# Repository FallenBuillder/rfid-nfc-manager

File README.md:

# rfid-nfc-manager
This repository consists of schematics, PCB layouts, code and 3D models for a rfid,nfc manager.

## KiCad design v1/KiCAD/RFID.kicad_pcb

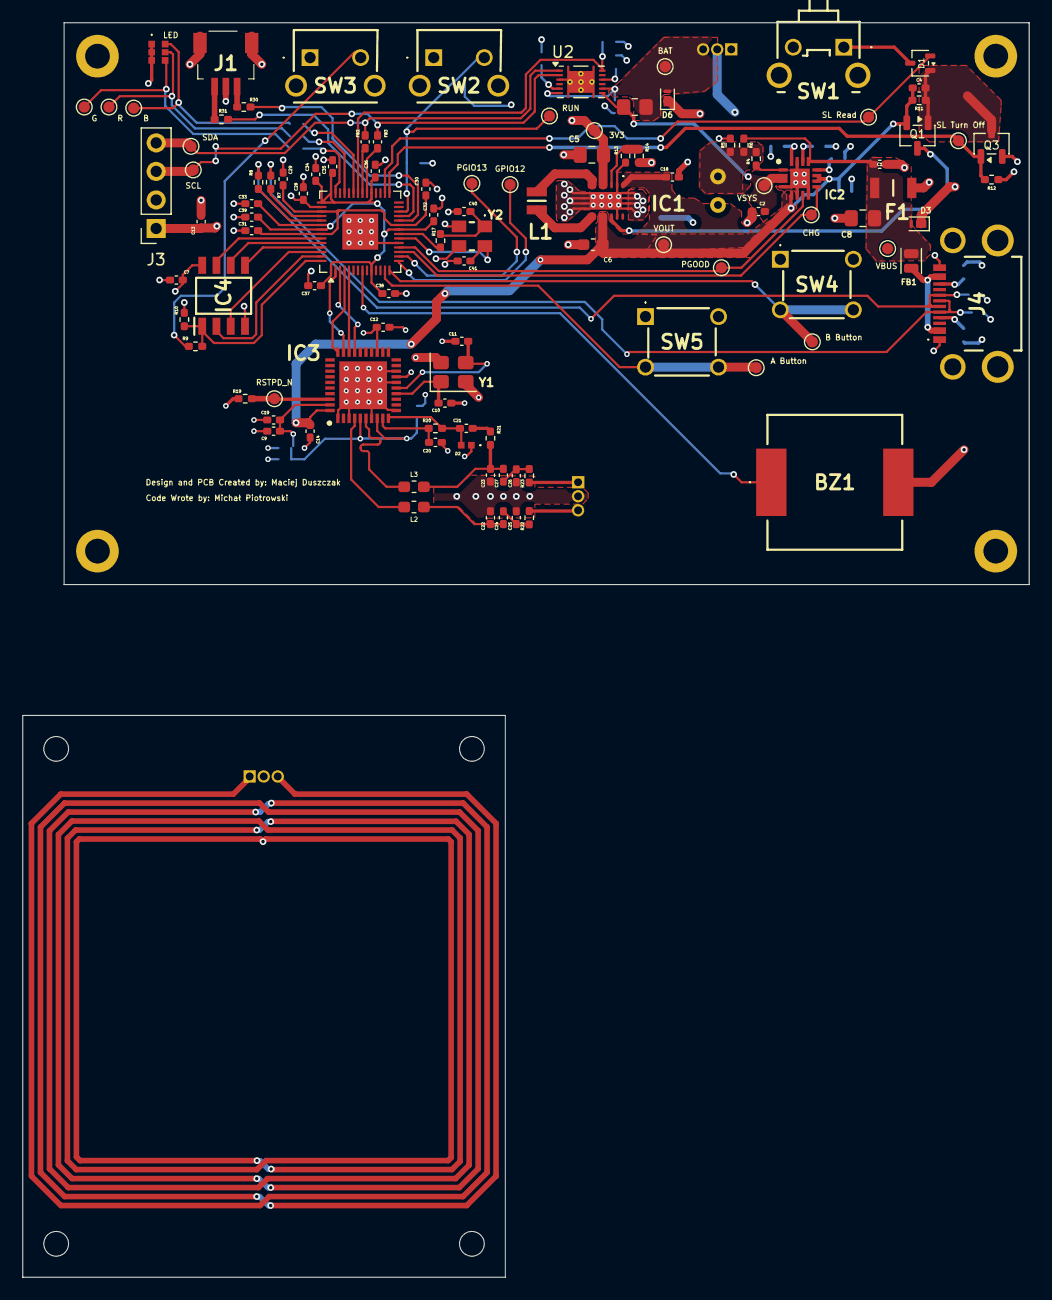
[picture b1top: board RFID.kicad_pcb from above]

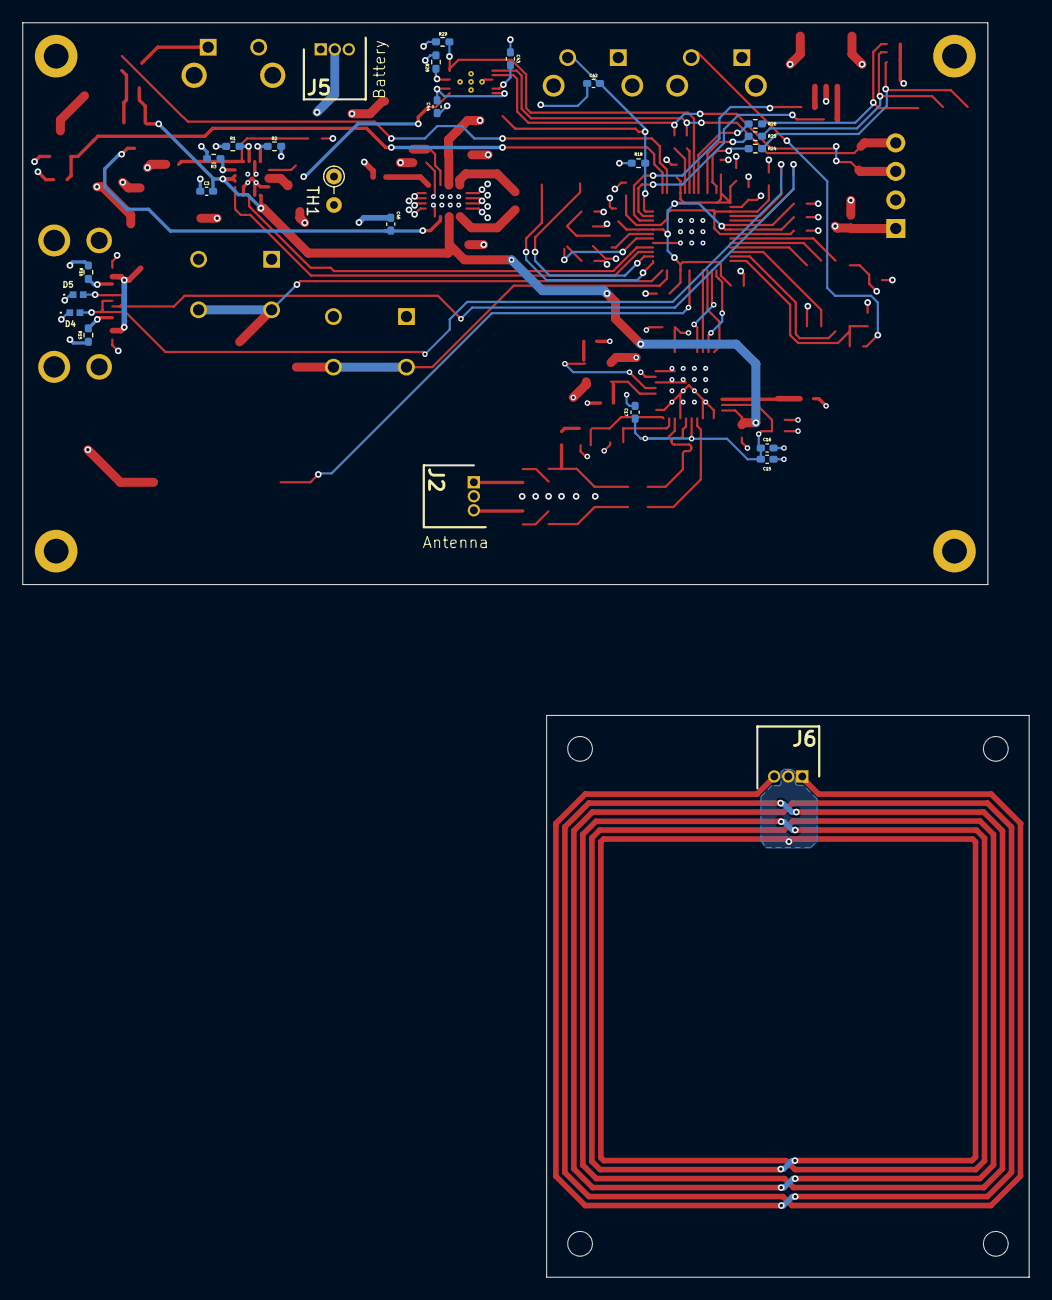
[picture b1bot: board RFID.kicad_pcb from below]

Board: 4 copper layers, 85.9 x 50.0 mm, 141 parts (25 on the bottom side), 83 nets.

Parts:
3V3: 3V3; TestPoint_Pad_D1.0mm
A Button: B_BTN; TestPoint_Pad_D1.0mm
B: BLUE; TestPoint_Pad_D1.0mm
B Button: A_BTN; TestPoint_Pad_D1.0mm
BAT: SRP; TestPoint_Pad_D1.0mm
BZ1: Buzzer; SMT1227T
C1, C28, C29, C34, C44: 1u; C_0402_1005Metric_Pad0.74x0.62mm_HandSolder
C2, C3, C16, C19: 4u7; C_0402_1005Metric_Pad0.74x0.62mm_HandSolder
C4, C7, C9, C12, C13, C14, C15, C17, C18, C20, C30, C31, C32, C33, C35, C36, C37, C38, C39, C42, C45: 100n; C_0402_1005Metric_Pad0.74x0.62mm_HandSolder
C5: 47u; C_0805_2012Metric_Pad1.18x1.45mm_HandSolder
C6: 22u; C_0603_1608Metric_Pad1.08x0.95mm_HandSolder
C8: 10u; C_0805_2012Metric_Pad1.18x1.45mm_HandSolder
C10, C11: 22p; C_0402_1005Metric_Pad0.74x0.62mm_HandSolder
C21: 1n; C_0402_1005Metric_Pad0.74x0.62mm_HandSolder
C22, C23: 220p; C_0402_1005Metric_Pad0.74x0.62mm_HandSolder
C24, C25, C26, C27: set; C_0402_1005Metric_Pad0.74x0.62mm_HandSolder
C40, C41: 15p; C_0402_1005Metric_Pad0.74x0.62mm_HandSolder
C43: 470n; C_0402_1005Metric_Pad0.74x0.62mm_HandSolder
CHG: CHG; TestPoint_Pad_D1.0mm
D1: BAT54CW; SOT-323_SC-70
D2, D4, D5: set; RCLAMP03331PWQC
D3: set; Nexperia_DSN1608-2_1.6x0.8mm
D6: 824520600; Nexperia_DSN1608-2_1.6x0.8mm
F1: 1A5 Hold; FUSC3216X70N
FB1: 100R; L_Changjiang_FTC201210S
FB2: 100-600R/100MHz; L_0402_1005Metric_Pad0.77x0.64mm_HandSolder
FB3: 600R; L_0402_1005Metric_Pad0.77x0.64mm_HandSolder
G: GREEN; TestPoint_Pad_D1.0mm
GPIO12: GPIO12; TestPoint_Pad_D1.0mm
H1, H2, H3, H4: MountingHole; MountingHole_2.2mm_M2_DIN965
H5, H6, H7, H8: MountingHole_Pad; MountingHole_2.2mm_M2_DIN965_Pad
IC1: TPS63020DSJR
IC2: BQ24075TRGTT; QFN50P300X300X100-17N-D
IC3: PN5321A3HN_C106,55; QFN50P600X600X100-41N-D
IC4: W25Q32JVSNIQ; SOIC127P600X175-8N
J1: JST SH Con; SM03BSRSSTBLFSN
J2, J6: Conn_01x03_Pin; SHDRRA3W35P0X125_1X3_550X550X350P
J3: Display Connector; PinSocket_1x04_P2.54mm_Vertical
J4: UJ20-C-H-G-MSMT-4B-P16-TR; UJ20CHGMSMT4BP16TR
J5: Battery Conenctor; SHDRRA3W35P0X125_1X3_550X550X350P
L1: 1u; 1285ASH1R0MP2
L2, L3: 560n; L_0603_1608Metric_Pad1.05x0.95mm_HandSolder
LED: RGB LED; INS66TFT5R5G5B
PGIO13: GPIO13; TestPoint_Pad_D1.0mm
PGOOD: PGOOD; TestPoint_Pad_D1.0mm
Q1: BSS84AK,215; SOT-23-3
Q3: NX7002AKVL; SOT-23-3
R: RED; TestPoint_Pad_D1.0mm
R1: 46k4; R_0402_1005Metric_Pad0.72x0.64mm_HandSolder
R2: 3k; R_0402_1005Metric_Pad0.72x0.64mm_HandSolder
R3: 1k1; R_0402_1005Metric_Pad0.72x0.64mm_HandSolder
R4, R11: 100k; R_0402_1005Metric_Pad0.72x0.64mm_HandSolder
R5: 11k; R_0402_1005Metric_Pad0.72x0.64mm_HandSolder
R6: 23k7; R_0402_1005Metric_Pad0.72x0.64mm_HandSolder
R7, R8: 27R; R_0402_1005Metric_Pad0.72x0.64mm_HandSolder
R9, R17, R20: 1k; R_0402_1005Metric_Pad0.72x0.64mm_HandSolder
R10, R18, R19, R28, R29: 10k; R_0402_1005Metric_Pad0.72x0.64mm_HandSolder
R12: 1M; R_0402_1005Metric_Pad0.72x0.64mm_HandSolder
R13: 137k; R_0402_1005Metric_Pad0.72x0.64mm_HandSolder
R14: 768k; R_0402_1005Metric_Pad0.72x0.64mm_HandSolder
R15, R16: 5k1; R_0402_1005Metric_Pad0.72x0.64mm_HandSolder
R21: 2k7; R_0402_1005Metric_Pad0.72x0.64mm_HandSolder
R22, R23: set; R_0402_1005Metric_Pad0.72x0.64mm_HandSolder
R24, R26, R30, R31: 100R; R_0402_1005Metric_Pad0.72x0.64mm_HandSolder
R25: 270R; R_0402_1005Metric_Pad0.72x0.64mm_HandSolder
R27: R01; R_0805_2012Metric_Pad1.20x1.40mm_HandSolder
RSTPD_N: RSTPD_N; TestPoint_Pad_D1.0mm
RUN: RUN; TestPoint_Pad_D1.0mm
SCL: SCL; TestPoint_Pad_D1.0mm
SDA: SDA; TestPoint_Pad_D1.0mm
SL Read: PL_Read; TestPoint_Pad_D1.0mm
SL Turn Off: Turn_Off; TestPoint_Pad_D1.0mm
SW1: SW_Push; B3F3152
SW2: RUN; TS11674105BK160RAD
SW3: BOOTSEL; TS11674105BK160RAD
SW4: A_BTN; TS016673BK160D
SW5: B_BTN; TS016673BK160D
TH1: 10k; R_Axial_DIN0204_L3.6mm_D1.6mm_P2.54mm_Vertical
U1: RP2040; QFN-56-1EP_7x7mm_P0.4mm_EP3.2x3.2mm
U2: BQ27441DRZR-G1A; Texas_S-PDSO-N12
VBUS: 5V; TestPoint_Pad_D1.0mm
VOUT: BQOUT; TestPoint_Pad_D1.0mm
VSYS: SRN; TestPoint_Pad_D1.0mm
Y1: 27M12; Crystal_SMD_TXC_7M-4Pin_3.2x2.5mm
Y2: 12M; ABM8272T3

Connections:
3V3: 3V3.1 (1_1), C5.1 (+), C7.2 (-), C12.1 (+), C13.2 (-), C28.1 (+), IC1.4 (VOUT_1), IC1.5 (VOUT_2), IC3.17 (I1), IC3.23 (PVDD), IC4.8 (VCC), J3.1, R10.2 (-), R14.1 (+), R18.2 (-), R19.2 (-), R29.1 (+), U1.44 (VREG_VIN)
/Battery Gauge/BAT: BAT.1 (1_1), C44.2 (-), D6.2 (A), J5.3, R27.1 (+), U2.6 (BAT), U2.8 (SRP)
/Battery Gauge/VSYS: C2.1 (+), IC2.2 (BAT_1), IC2.3 (BAT_2), R27.2 (-), U2.7 (SRN), VSYS.1 (1_1)
/Buck-Boost/EN: C45.1 (+), IC1.12 (EN), Q1.3 (D)
/Buck-Boost/IN: C3.1 (+), C4.1 (+), C6.1 (+), C14.2 (-), C18.1 (+), IC1.1 (VINA), IC1.10 (VIN_1), IC1.11 (VIN_2), IC2.5 (EN2), IC2.10 (OUT_1), IC2.11 (OUT_2), IC3.40 (VBAT), Q1.2 (S), R11.1 (+), VOUT.1 (1_1)
/CHG: CHG.1 (1_1), IC2.9 (~CHG), U1.17 (GPIO14)
/CS: IC4.1 (~CS), R9.1 (+), R10.1 (+), U1.56 (~QSPI_SS)
/D+: D5.2 (A2), J4.A6 (DP1), J4.B6 (DP2), R8.2 (-)
/D-: D4.2 (A2), J4.A7 (DN1), J4.B7 (DN2), R7.1 (+)
/GPOUT: R29.2 (-), U1.36 (GPIO24), U2.12 (GPOUT)
/IO0: IC4.5 (DI_(IO0)), U1.53 (QSPI_SD0)
/IO1: IC4.2 (DO_(IO1)), U1.55 (QSPI_SD1)
/IO2: IC4.3 (~WP_(IO2)), U1.54 (QSPI_SD2)
/IO3: IC4.7 (~HOLD_OR_/RESET_(IO3)), U1.51 (QSPI_SD3)
/MISO: IC3.29 (MISO_/_P71), U1.2 (GPIO0)
/MOSI: IC3.28 (MOSI_/_SDA_/_HSU_TX), U1.5 (GPIO3)
/NSS: IC3.27 (NSS_/_P50_SCL_/_HSU_RX), U1.3 (GPIO1)
/PGOOD: IC2.7 (~PGOOD), PGOOD.1 (1_1), U1.18 (GPIO15)
/Power Switch/IN: C1.1 (+), C8.1 (+), D3.2 (A), F1.1, FB1.2, IC2.13 (IN), R6.1 (+)
/RFID/TX1: IC3.4 (TX1), L2.1 (+)
/RFID/TX2: IC3.6 (TX2), L3.1 (+)
/SCK: IC3.30 (SCK_/_P72), U1.4 (GPIO2)
/SCL: FB3.2, J3.3, SCL.1 (1_1), U2.2 (SCL)
/SDA: FB2.2, J3.4, SDA.1 (1_1), U2.1 (SDA)
/SL_Read: D1.2, SL Read.1 (1_1), U1.30 (GPIO19)
/SPI_CLK: IC4.6 (CLK), U1.52 (QSPI_SCLK)
/Turn_Off: Q3.1 (G), R12.1 (+), SL Turn Off.1 (1_1), U1.29 (GPIO18)
/USB/CC1: J4.A5 (CC1), R15.1 (+)
/USB/CC2: J4.B5 (CC2), R16.2 (-)
/USB/VBUS_USB: FB1.1, J4.A4 (VBUS_1), J4.B4 (VBUS_2)
GND: BZ1.2 (-), C1.2 (-), C2.2 (-), C3.2 (-), C5.2 (-), C6.2 (-), C7.1 (+), C8.2 (-), C9.2 (-), C10.1 (+), C11.1 (+), C12.2 (-), C13.1 (+), C14.1 (+), C15.2 (-), C16.2 (-), C17.2 (-), C18.2 (-), C19.1 (+), C20.2 (-), C22.1 (+), C23.2 (-), C25.1 (+), C26.2 (-), C28.2 (-), C29.2 (-), C30.2 (-), C31.2 (-), C32.1 (+), C33.1 (+), C34.2 (-), C35.1 (+), C36.1 (+), C37.2 (-), C38.2 (-), C39.2 (-), C40.1 (+), C41.1 (+), C42.2 (-), C43.1 (+), C44.1 (+), C45.2 (-), D2.1 (A1), D3.1 (K), D4.1 (A1), D5.1 (A1), D6.1 (K), F1.2, H5.1 (1_1), H6.1 (1_1), H7.1 (1_1), H8.1 (1_1), IC1.2 (GND), IC1.13 (PS/SYNC), IC1.15 (PGND_1), IC1.16 (PGND_2), IC1.17 (PGND_3), IC1.18 (PGND_4), IC1.19 (PGND_5), IC1.20 (PGND_6), IC1.21 (PGND_7), IC1.22 (PGND_8), IC1.23 (PGND_9), IC2.4 (~CE), IC2.6 (EN1), IC2.8 (VSS), IC2.15 (SYSOFF), IC2.17 (EP), IC3.1 (DVSS), IC3.3 (TVSS1), IC3.7 (TVSS2), IC3.11 (AVSS), IC3.16 (I0), IC3.18 (TESTEN), IC3.41 (EPAD), IC4.4 (GND), J1.2, J1.MP1, J1.MP2, J2.2, J3.2, J4.A1 (GND_1), J4.B1 (GND_2), J4.MH1 (MH_1), J4.MH2 (MH_2), J4.MH3 (MH_3), J4.MH4 (MH_4), J5.2, LED.1 (K_BLUE), LED.2 (K_RED_), LED.3 (K_GREEN), Q3.2 (S), R1.1 (+), R2.1 (+), R3.2 (-), R5.2 (-), R12.2 (-), R13.2 (-), R15.2 (-), R16.1 (+), R28.1 (+), SW1.2, SW1.3 (K), SW1.4 (A), SW2.1, SW2.3 (K), SW2.4 (A), SW3.1, SW3.3 (K), SW3.4 (A), SW4.1, SW4.2, SW5.1, SW5.2, TH1.2, U1.19 (TESTEN), U1.57 (GND), U2.3 (V_{SS}), U2.13 (PAD), Y1.2 (G), Y1.4 (G), Y2.2 (G), Y2.3 (G)
unnamed: BZ1.1 (+), U1.8 (GPIO6)
unnamed: C4.2 (-), D1.1, Q1.1 (G), Q3.3 (D), R11.2 (-)
unnamed: C10.2 (-), IC3.14 (OSCIN), Y1.1
unnamed: C11.2 (-), IC3.15 (OSCOUT), Y1.3
unnamed: C9.1 (+), C15.1 (+), C16.1 (+), C17.1 (+), C19.2 (-), IC3.5 (TVDD), IC3.8 (AVDD), IC3.39 (DVDD)
unnamed: C20.1 (+), IC3.9 (VMID), R20.2 (-)
unnamed: C21.1 (+), R21.2 (-)
unnamed: C21.2 (-), D2.2 (A2), IC3.10 (RX), R20.1 (+)
unnamed: C22.2 (-), C24.2 (-), L2.2 (-)
unnamed: C23.1 (+), C27.1 (+), L3.2 (-), R21.1 (+)
unnamed: C24.1 (+), C25.2 (-), R22.2 (-)
unnamed: C26.1 (+), C27.2 (-), R23.2 (-)
unnamed: C29.1 (+), C30.1 (+), C31.1 (+), U1.23 (DVDD), U1.45 (VREG_VOUT), U1.50 (DVDD)
unnamed: C32.2 (-), C33.2 (-), C34.1 (+), C35.2 (-), C36.2 (-), C37.1 (+), C38.1 (+), C39.1 (+), U1.1 (IOVDD), U1.10 (IOVDD), U1.22 (IOVDD), U1.33 (IOVDD), U1.42 (IOVDD), U1.43 (ADC_AVDD), U1.48 (USB_VDD), U1.49 (IOVDD)
unnamed: C40.2 (-), R17.1 (+), Y2.1
unnamed: C41.2 (-), U1.20 (XIN), Y2.4
unnamed: C42.1 (+), R18.1 (+), RUN.1 (1_1), SW2.2, U1.26 (RUN)
unnamed: C43.2 (-), U2.5 (V_{DD})
unnamed: D1.3, SW1.1
unnamed: IC1.3 (FB), R13.1 (+), R14.2 (-)
unnamed: IC1.8 (L1_1), IC1.9 (L1_2), L1.1
unnamed: IC1.6 (L2_1), IC1.7 (L2_2), L1.2
unnamed: IC2.12 (ILIM), R3.1 (+)
unnamed: IC2.16 (ISET), R2.2 (-)
unnamed: IC2.14 (TMR), R1.2 (-)
unnamed: IC2.1 (TS), R4.1 (+)
unnamed: IC3.38 (RSTPD_N), R19.1 (+), RSTPD_N.1 (1_1)
unnamed: J2.1, R23.1 (+)
unnamed: J2.3, R22.1 (+)
unnamed: J6.1, J6.2, J6.3
unnamed: B.1 (1_1), LED.4 (A_BLUE), R26.2 (-)
unnamed: G.1 (1_1), LED.6 (A_GREEN), R24.2 (-)
unnamed: LED.5 (A_RED), R.1 (1_1), R25.2 (-)
unnamed: R4.2 (-), R5.1 (+), R6.2 (-), TH1.1
unnamed: R7.2 (-), U1.46 (USB_DM)
unnamed: R8.1 (+), U1.47 (USB_DP)
unnamed: R9.2 (-), SW3.2
unnamed: R17.2 (-), U1.21 (XOUT)
unnamed: R24.1 (+), U1.41 (GPIO29/ADC3)
unnamed: R25.1 (+), U1.39 (GPIO27/ADC1)
unnamed: R26.1 (+), U1.37 (GPIO25)
unnamed: R28.2 (-), U2.10 (BIN)
unnamed: J1.1, R30.1 (+)
unnamed: R30.2 (-), U1.24 (SWCLK)
unnamed: J1.3, R31.1 (+)
unnamed: R31.2 (-), U1.25 (SWDIO)
unnamed: B Button.1 (1_1), SW4.3 (K), SW4.4 (A), U1.14 (GPIO11)
unnamed: A Button.1 (1_1), SW5.3 (K), SW5.4 (A), U1.13 (GPIO10)
unnamed: GPIO12.1 (1_1), U1.15 (GPIO12)
unnamed: PGIO13.1 (1_1), U1.16 (GPIO13)
unnamed: FB3.1, U1.34 (GPIO22)
unnamed: FB2.1, U1.35 (GPIO23)

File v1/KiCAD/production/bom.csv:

Designator,Footprint,Quantity,Value,LCSC Part #
3V3,TestPoint_Pad_D1.0mm,1,3V3,
A BUTTON,TestPoint_Pad_D1.0mm,1,B_BTN,
B,TestPoint_Pad_D1.0mm,1,BLUE,
B BUTTON,TestPoint_Pad_D1.0mm,1,A_BTN,
BAT,TestPoint_Pad_D1.0mm,1,SRP,
BZ1,SMT1227T,1,Buzzer,
"C1, C28, C29, C34, C44",0402,5,1u,
"C10, C11",0402,2,22p,
"C12, C13, C14, C15, C17, C20, C30, C31, C32, C33, C35, C36, C37, C38, C39, C4, C42, C7, C9",0402,19,100n,
"C16, C19, C2, C3",0402,4,4u7,
"C18, C45",0805,2,100n,
C21,0402,1,1n,
"C22, C23",0402,2,220p,
"C24, C25, C26, C27, R22, R23",0402,6,set,
"C40, C41",0402,2,15p,
C43,0402,1,470n,
C5,0805,1,47u,
C6,0603,1,22u,
C8,0805,1,10u,
CHG,TestPoint_Pad_D1.0mm,1,CHG,
D1,SOT-323_SC-70,1,BAT54CW,
"D2, D4, D5",RCLAMP03331PWQC,3,set,
D3,Nexperia_DSN1608-2_1.6x0.8mm,1,set,
D6,Nexperia_DSN1608-2_1.6x0.8mm,1,824520600,
F1,FUSC3216X70N,1,1A5 Hold,
FB1,L_Changjiang_FTC201210S,1,100R,
FB2,0402,1,100-600R/100MHz,
FB3,0402,1,600R,
G,TestPoint_Pad_D1.0mm,1,GREEN,
GPIO12,TestPoint_Pad_D1.0mm,1,GPIO12,
IC1,TPS63020DSJR,1,TPS63020DSJR,
IC2,QFN50P300X300X100-17N-D,1,BQ24075TRGTT,
IC3,QFN50P600X600X100-41N-D,1,"PN5321A3HN_C106,55",
IC4,SOIC127P600X175-8N,1,W25Q32JVSNIQ,
J1,SM03BSRSSTBLFSN,1,JST SH Con,
"J2, J6",SHDRRA3W35P0X125_1X3_550X550X350P,2,Conn_01x03_Pin,
J3,PinSocket_1x04_P2.54mm_Vertical,1,Display Connector,
J4,UJ20CHGMSMT4BP16TR,1,UJ20-C-H-G-MSMT-4B-P16-TR,
J5,SHDRRA3W35P0X125_1X3_550X550X350P,1,Battery Conenctor,
L1,1285ASH1R0MP2,1,1u,
"L2, L3",0603,2,560n,
LED,INS66TFT5R5G5B,1,RGB LED,
PGIO13,TestPoint_Pad_D1.0mm,1,GPIO13,
PGOOD,TestPoint_Pad_D1.0mm,1,PGOOD,
Q1,SOT-23-3,1,"BSS84AK,215",
Q3,SOT-23-3,1,NX7002AKVL,
R,TestPoint_Pad_D1.0mm,1,RED,
R1,0402,1,46k8,
"R10, R18, R19, R28, R29",0402,5,10k,
"R11, R4",0402,2,100k,
R12,0402,1,1M,
R13,0402,1,137k,
R14,0402,1,768k,
"R15, R16",0402,2,5k1,
"R17, R20, R9",0402,3,1k,
R2,0402,1,3k,
R21,0402,1,2k7,
"R24, R26, R30, R31",0402,4,100R,
R25,0402,1,270R,
R27,0805,1,R01,
R3,0402,1,1k1,
R5,0402,1,11k,
R6,0402,1,23k7,
"R7, R8",0402,2,27R,
RSTPD_N,TestPoint_Pad_D1.0mm,1,RSTPD_N,
RUN,TestPoint_Pad_D1.0mm,1,RUN,
SCL,TestPoint_Pad_D1.0mm,1,SCL,
SDA,TestPoint_Pad_D1.0mm,1,SDA,
SL READ,TestPoint_Pad_D1.0mm,1,PL_Read,
SL TURN OFF,TestPoint_Pad_D1.0mm,1,Turn_Off,
SW1,B3F3152,1,SW_Push,
SW2,TS11674105BK160RAD,1,RUN,
SW3,TS11674105BK160RAD,1,BOOTSEL,
SW4,TS016673BK160D,1,A_BTN,
SW5,TS016673BK160D,1,B_BTN,
TH1,R_Axial_DIN0204_L3.6mm_D1.6mm_P2.54mm_Vertical,1,10k,
U1,QFN-56-1EP_7x7mm_P0.4mm_EP3.2x3.2mm,1,RP2040,
U2,Texas_S-PDSO-N12,1,BQ27441DRZR-G1A,
VBUS,TestPoint_Pad_D1.0mm,1,5V,
VOUT,TestPoint_Pad_D1.0mm,1,BQOUT,
VSYS,TestPoint_Pad_D1.0mm,1,SRN,
Y1,Crystal_SMD_TXC_7M-4Pin_3.2x2.5mm,1,27M12,
Y2,ABM8272T3,1,12M,
